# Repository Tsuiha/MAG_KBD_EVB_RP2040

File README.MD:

# vial-qmkとRP2040で作る磁気キーボード

rp2040とmuxを使用して作る磁気キーボード用の設計情報です。
簡単なguideにpdfも入れています。

firmwareはvial-qmkのforkです。
[firmware](https://github.com/Tsuiha/vial-qmk/tree/he/keyboards/0_he_rp2040/mag_kbd_evb)

[software](https://tsuiha.github.io/qmagk_configlator/)

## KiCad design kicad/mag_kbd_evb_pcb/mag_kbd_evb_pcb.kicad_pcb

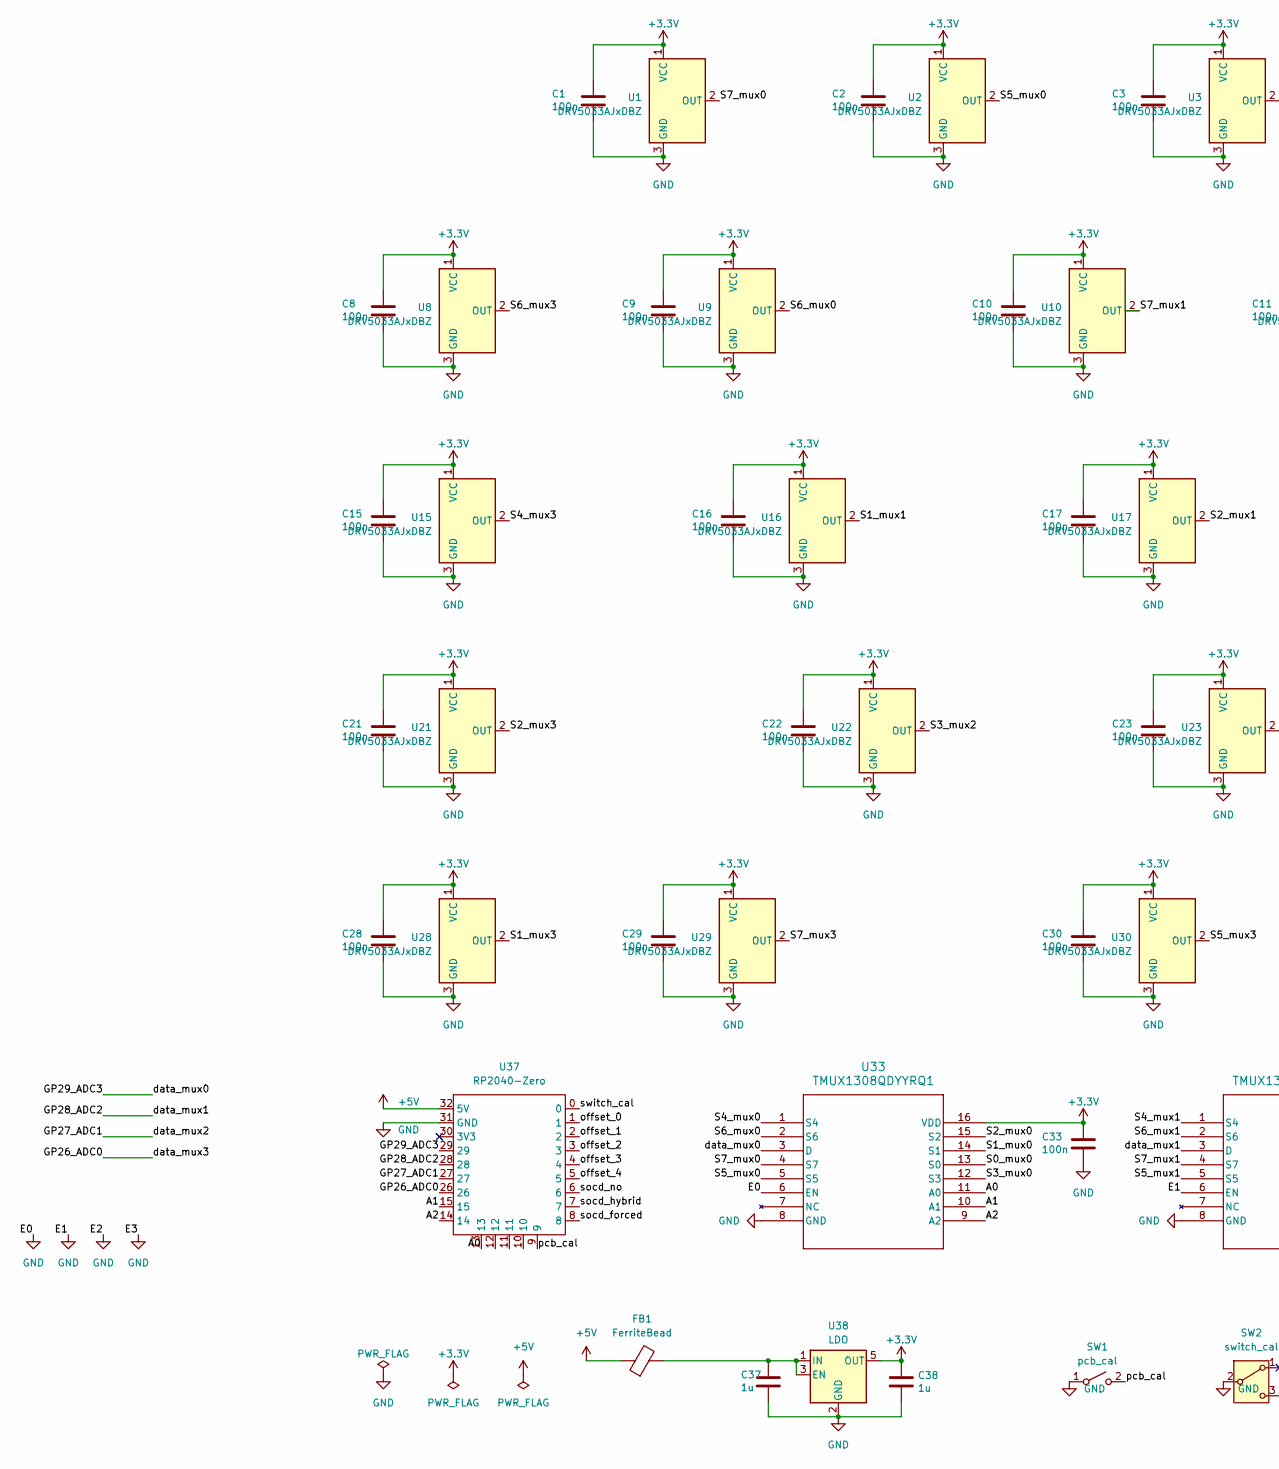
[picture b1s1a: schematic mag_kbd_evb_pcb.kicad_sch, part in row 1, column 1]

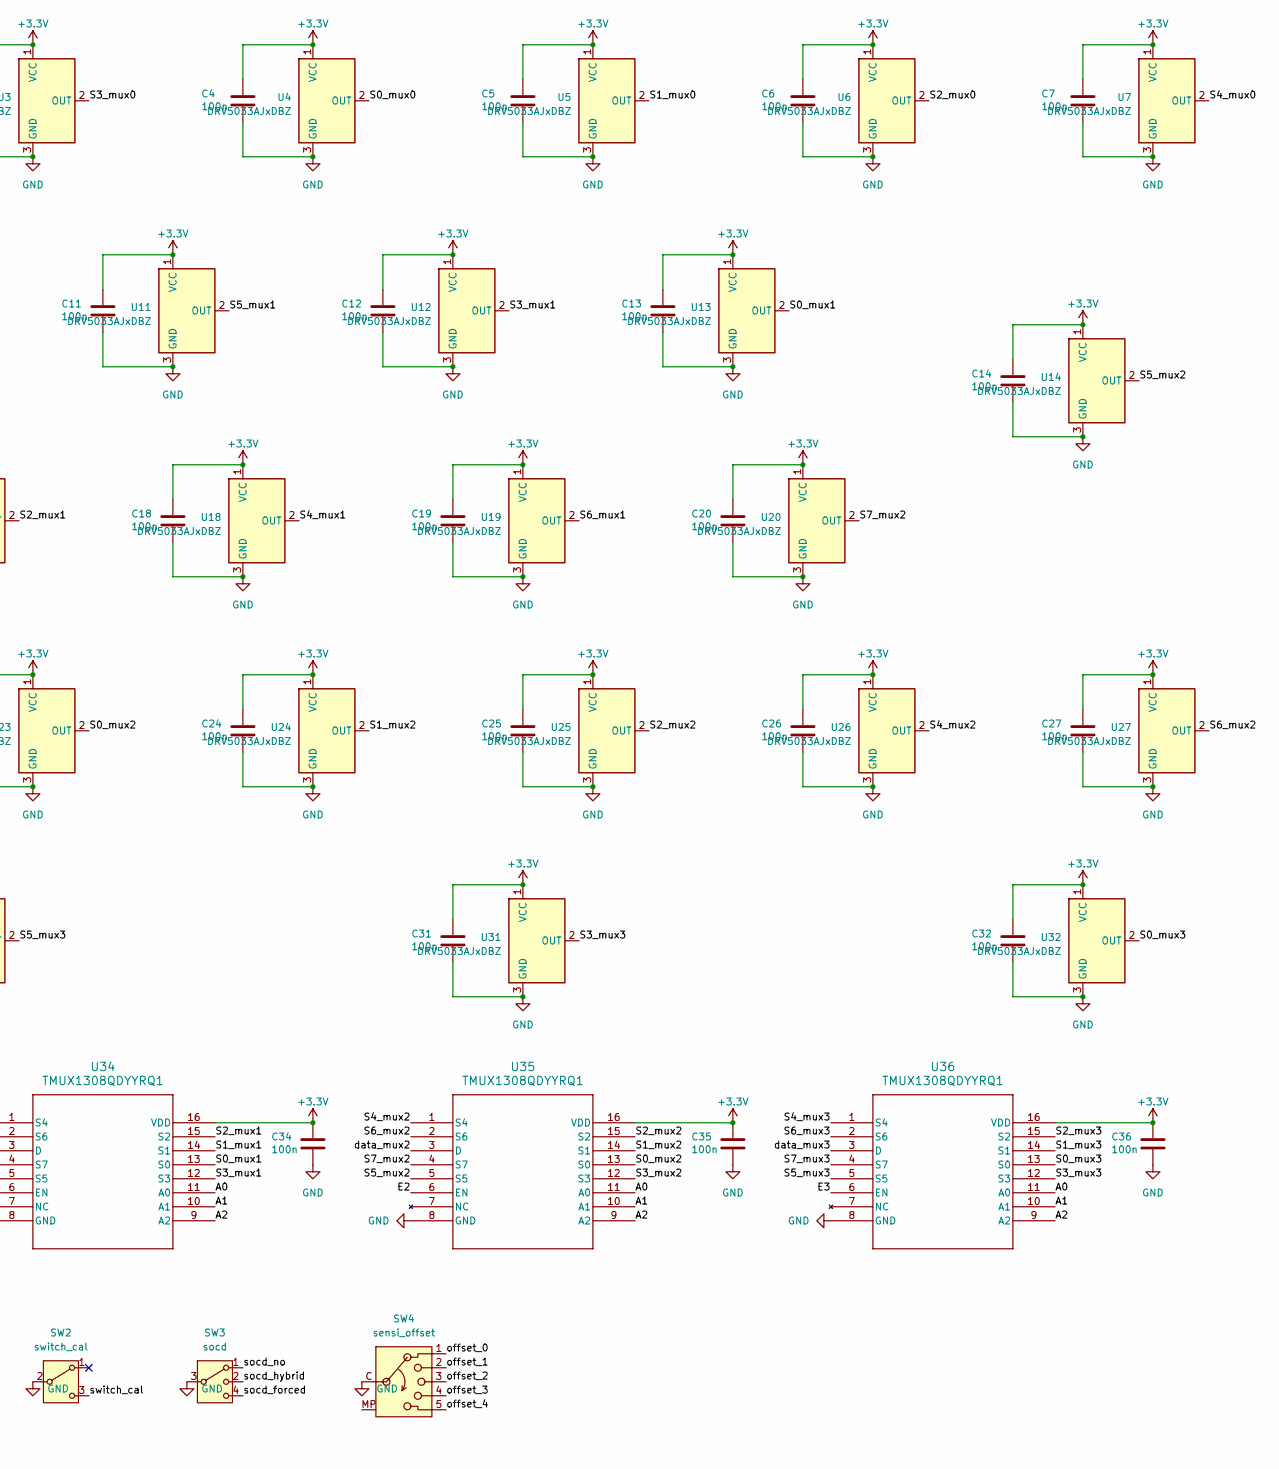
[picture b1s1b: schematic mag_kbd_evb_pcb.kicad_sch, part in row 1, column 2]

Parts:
C1, C2, C3, C4, C5, C6, C7, C8, C9, C10, C11, C12, C13, C14, C15, C16, C17, C18, C19, C20, C21, C22, C23, C24, C25, C26, C27, C28, C29, C30, C31, C32, C33, C34, C35, C36: 100n; C_0603_1608Metric
C37, C38: 1u; C_0603_1608Metric
FB1: FerriteBead; C_0603_1608Metric
SW1: pcb_cal; SW_SPST_SKQG_WithStem
SW2: switch_cal; SHOUHAN_SK12D
SW3: socd; SHOUHAN_SK13D
SW4: sensi_offset; SHOUHAN_SK15D
U1, U2, U3, U4, U5, U6, U7, U8, U9, U10, U11, U12, U13, U14, U15, U16, U17, U18, U19, U20, U21, U22, U23, U24, U25, U26, U27, U28, U29, U30, U31, U32: DRV5033AJxDBZ; hallsensor_hall
U33, U34, U35, U36: TMUX1308QDYYRQ1; Texas_DYY0016A_TSOT-23-16_4.2x2.0mm_P0.5mm
U37: RP2040-Zero
U38: LDO; SOT-23-5

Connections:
+3.3V: C1.1, C2.1, C3.1, C4.1, C5.1, C6.1, C7.1, C8.1, C9.1, C10.1, C11.1, C12.1, C13.1, C14.1, C15.1, C16.1, C17.1, C18.1, C19.1, C20.1, C21.1, C22.1, C23.1, C24.1, C25.1, C26.1, C27.1, C28.1, C29.1, C30.1, C31.1, C32.1, C33.1, C34.1, C35.1, C36.1, C38.1, U1.1 (VCC), U2.1 (VCC), U3.1 (VCC), U4.1 (VCC), U5.1 (VCC), U6.1 (VCC), U7.1 (VCC), U8.1 (VCC), U9.1 (VCC), U10.1 (VCC), U11.1 (VCC), U12.1 (VCC), U13.1 (VCC), U14.1 (VCC), U15.1 (VCC), U16.1 (VCC), U17.1 (VCC), U18.1 (VCC), U19.1 (VCC), U20.1 (VCC), U21.1 (VCC), U22.1 (VCC), U23.1 (VCC), U24.1 (VCC), U25.1 (VCC), U26.1 (VCC), U27.1 (VCC), U28.1 (VCC), U29.1 (VCC), U30.1 (VCC), U31.1 (VCC), U32.1 (VCC), U33.16 (VDD), U34.16 (VDD), U35.16 (VDD), U36.16 (VDD), U38.5 (OUT)
+5V: FB1.1, U37.32 (5V)
/A0: U33.11 (A0), U34.11 (A0), U35.11 (A0), U36.11 (A0), U37.13
/A1: U33.10 (A1), U34.10 (A1), U35.10 (A1), U36.10 (A1), U37.15
/A2: U33.9 (A2), U34.9 (A2), U35.9 (A2), U36.9 (A2), U37.14
/GP26_ADC0: U36.3 (D), U37.26
/GP27_ADC1: U35.3 (D), U37.27
/GP28_ADC2: U34.3 (D), U37.28
/GP29_ADC3: U33.3 (D), U37.29
/S0_mux0: U4.2 (OUT), U33.13 (S0)
/S0_mux1: U13.2 (OUT), U34.13 (S0)
/S0_mux2: U23.2 (OUT), U35.13 (S0)
/S0_mux3: U32.2 (OUT), U36.13 (S0)
/S1_mux0: U5.2 (OUT), U33.14 (S1)
/S1_mux1: U16.2 (OUT), U34.14 (S1)
/S1_mux2: U24.2 (OUT), U35.14 (S1)
/S1_mux3: U28.2 (OUT), U36.14 (S1)
/S2_mux0: U6.2 (OUT), U33.15 (S2)
/S2_mux1: U17.2 (OUT), U34.15 (S2)
/S2_mux2: U25.2 (OUT), U35.15 (S2)
/S2_mux3: U21.2 (OUT), U36.15 (S2)
/S3_mux0: U3.2 (OUT), U33.12 (S3)
/S3_mux1: U12.2 (OUT), U34.12 (S3)
/S3_mux2: U22.2 (OUT), U35.12 (S3)
/S3_mux3: U31.2 (OUT), U36.12 (S3)
/S4_mux0: U7.2 (OUT), U33.1 (S4)
/S4_mux1: U18.2 (OUT), U34.1 (S4)
/S4_mux2: U26.2 (OUT), U35.1 (S4)
/S4_mux3: U15.2 (OUT), U36.1 (S4)
/S5_mux0: U2.2 (OUT), U33.5 (S5)
/S5_mux1: U11.2 (OUT), U34.5 (S5)
/S5_mux2: U14.2 (OUT), U35.5 (S5)
/S5_mux3: U30.2 (OUT), U36.5 (S5)
/S6_mux0: U9.2 (OUT), U33.2 (S6)
/S6_mux1: U19.2 (OUT), U34.2 (S6)
/S6_mux2: U27.2 (OUT), U35.2 (S6)
/S6_mux3: U8.2 (OUT), U36.2 (S6)
/S7_mux0: U1.2 (OUT), U33.4 (S7)
/S7_mux1: U10.2 (OUT), U34.4 (S7)
/S7_mux2: U20.2 (OUT), U35.4 (S7)
/S7_mux3: U29.2 (OUT), U36.4 (S7)
/offset_0: SW4.1, U37.1
/offset_1: SW4.2, U37.2
/offset_2: SW4.3, U37.3
/offset_3: SW4.4, U37.4
/offset_4: SW4.5, U37.5
/pcb_cal: SW1.2 (B), U37.9
/socd_forced: SW3.4, U37.8
/socd_hybrid: SW3.2, U37.7
/socd_no: SW3.1, U37.6
/switch_cal: SW2.3 (C), U37.0
GND: C1.2, C2.2, C3.2, C4.2, C5.2, C6.2, C7.2, C8.2, C9.2, C10.2, C11.2, C12.2, C13.2, C14.2, C15.2, C16.2, C17.2, C18.2, C19.2, C20.2, C21.2, C22.2, C23.2, C24.2, C25.2, C26.2, C27.2, C28.2, C29.2, C30.2, C31.2, C32.2, C33.2, C34.2, C35.2, C36.2, C37.2, C38.2, SW1.1 (A), SW2.2 (B), SW3.3, SW4.C (Common), U1.3 (GND), U2.3 (GND), U3.3 (GND), U4.3 (GND), U5.3 (GND), U6.3 (GND), U7.3 (GND), U8.3 (GND), U9.3 (GND), U10.3 (GND), U11.3 (GND), U12.3 (GND), U13.3 (GND), U14.3 (GND), U15.3 (GND), U16.3 (GND), U17.3 (GND), U18.3 (GND), U19.3 (GND), U20.3 (GND), U21.3 (GND), U22.3 (GND), U23.3 (GND), U24.3 (GND), U25.3 (GND), U26.3 (GND), U27.3 (GND), U28.3 (GND), U29.3 (GND), U30.3 (GND), U31.3 (GND), U32.3 (GND), U33.6 (EN), U33.8 (GND), U34.6 (EN), U34.8 (GND), U35.6 (EN), U35.8 (GND), U36.6 (EN), U36.8 (GND), U37.31 (GND), U38.2 (GND)
unnamed: C37.1, FB1.2, U38.1 (IN), U38.3 (EN)

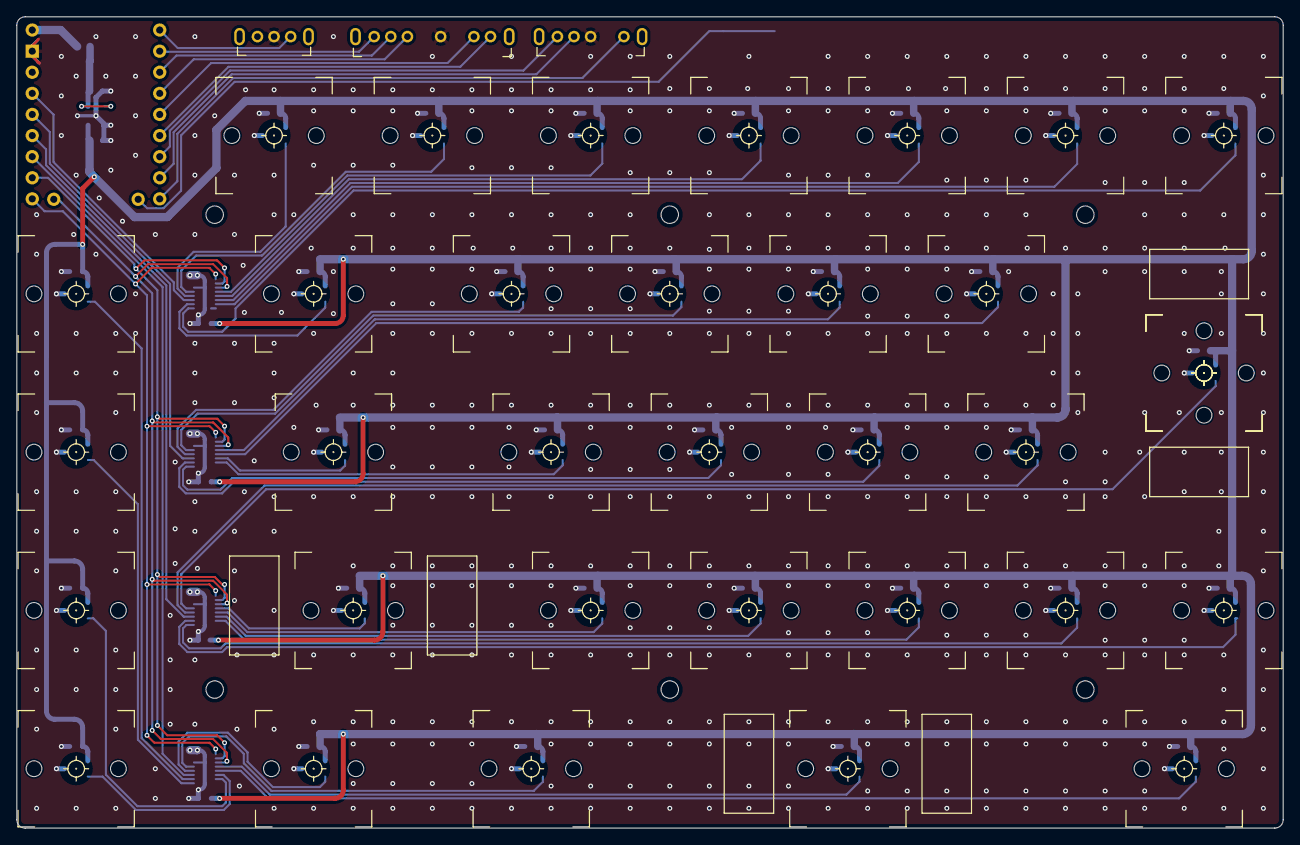
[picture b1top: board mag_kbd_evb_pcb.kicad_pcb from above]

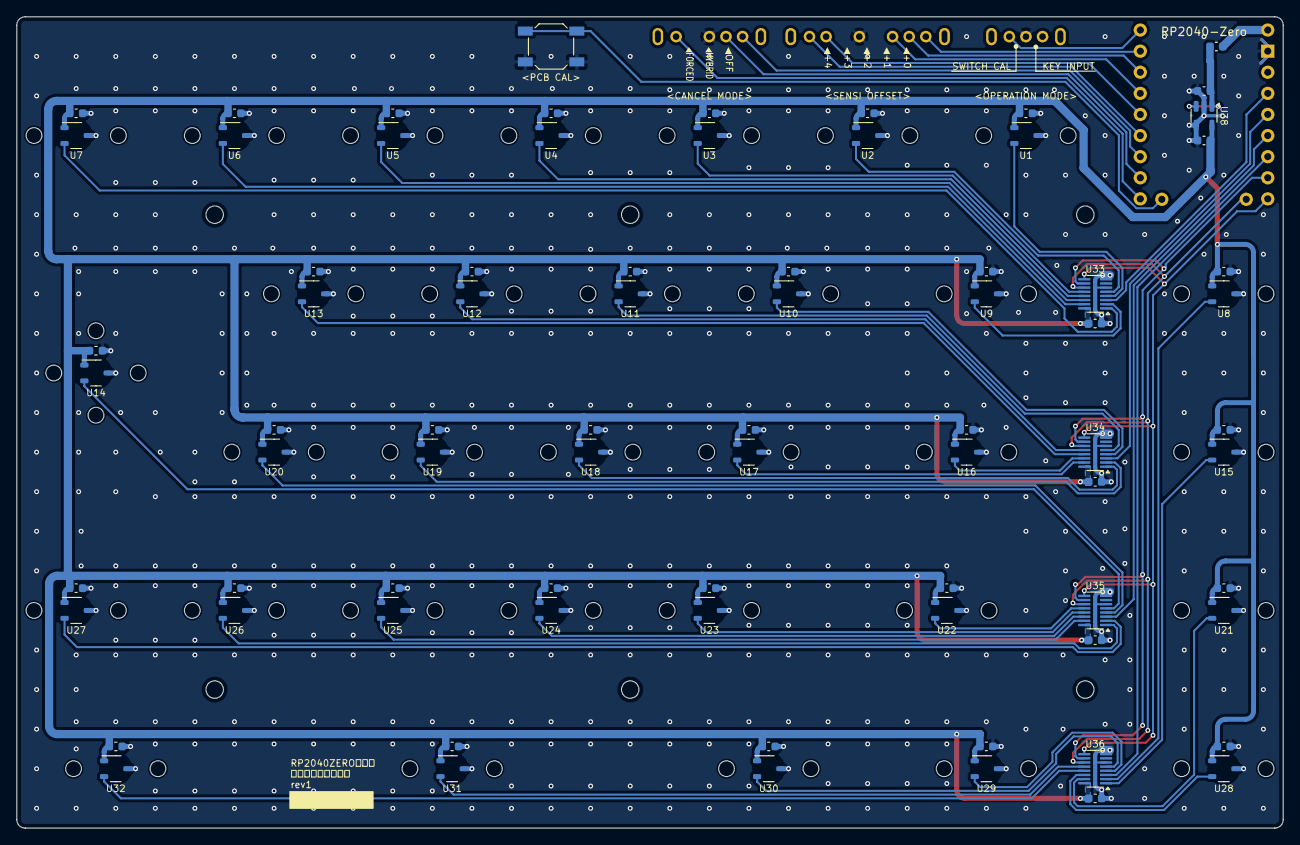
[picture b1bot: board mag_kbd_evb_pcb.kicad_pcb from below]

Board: 2 copper layers, 152.4 x 97.6 mm, 114 parts (77 on the bottom side), 53 nets.

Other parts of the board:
SW6, SW6#2, SW6#3, SW6#4, SW6#5, SW6#6, SW6#7, SW6#8, SW6#10, SW6#11, SW6#12, SW6#14, SW6#15, SW6#16, SW6#17, SW6#18, SW6#19, SW6#21, SW6#22, SW6#25, SW6#26, SW6#27, SW6#29, SW6#32, SW6#33: SW_PUSH; Magnetic_switch_hole_c
SW6#9: SW_PUSH; Magnetic_switch_hole_c_2
SW6#13: SW_PUSH; Magnetic_switch_hole_c_ISO
SW6#20, SW6#24, SW6#28: SW_PUSH; Magnetic_switch_hole_c_15
SW6#23: SW_PUSH; Magnetic_switch_hole_c_125
SW6#30: SW_PUSH; Magnetic_switch_hole_c_175
SW6#31: SW_PUSH; Magnetic_switch_hole_c_275
